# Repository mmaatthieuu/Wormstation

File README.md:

# Wormstation

A fully open-source, all-in-one platform designed for **ease of use** and **accessibility**, yet offering **powerful, highly automated** solutions for laboratory-grade biological research. Wormstation is **ideal for high-throughput workflows** and **streamlined experimental processes**, particularly in _C. elegans_ studies and other small model organisms.

---

## Repositories

- **Wormstation Controller**  
  [GitHub: wormstation_controller](https://github.com/mmaatthieuu/wormstation_controller)  
  A user-friendly GUI that remotely controls the Wormstation Client software. It manages camera and LED settings, schedules recordings, and facilitates error checks or updates—all from a single interface.

- **Wormstation Client**  
  [GitHub: wormstation_client](https://github.com/mmaatthieuu/wormstation_client)  
  The client software running on each Wormstation device (e.g., Raspberry Pi). It handles local camera captures, LED strobing or continuous illumination, data compression, and robust logging routines.

---

## Hardware Overview

Below is an example Wormstation hardware setup, illustrating the 3D-printed housing, integrated cameras, LED arrays, and other key components:

The complete mechanical and electronic designs (including 3D-printable files and KiCad schematics) are maintained in this repository, making the project fully open and reproducible.

---

## Key Features

- **High-Throughput**  
  Record multiple worms in parallel with automated capture schedules and minimal user intervention.
- **Fully Open-Source**  
  All code, hardware designs, and documentation are freely available for community-driven improvements.
- **Modular & Extensible**  
  Easily replace or upgrade components, adapt the software for new experimental protocols, or integrate additional sensors/actuators.
- **Optogenetics & Advanced Illumination**  
  Precisely control IR, blue, and orange LEDs for non-disruptive observation or targeted neural stimulation.
- **Comprehensive Logging**  
  Both the controller and the client track system status, events, and errors, aiding reproducibility and troubleshooting.

---

## Getting Started

1. **Hardware Assembly**  
   - Print the parts (`3D_print/` directory) and assemble according to the provided instructions.
   - Populate the PCB using KiCad files and a bill of materials found in the `electronics/` directory.
   - Mount the cameras, LED rings, or other illumination modules as described in the hardware guides.

2. **Software Installation**  
   - Set up the [Wormstation Client](https://github.com/mmaatthieuu/wormstation_client) on each device (e.g., Raspberry Pi).
   - Use the [Wormstation Controller](https://github.com/mmaatthieuu/wormstation_controller) GUI on your PC for centralized management.

3. **Configuration**  
   - Provide network addresses or hostnames in a `hosts.txt` file so the controller can detect each Wormstation on the LAN or VPN.
   - Customize recording schedules, LED parameters, and log verbosity per your research needs.

4. **Run Experiments**  
   - Start the controller application, select the devices, and define the experimental parameters.
   - Monitor live frames or single-shot previews to check focus/illumination.
   - Retrieve data automatically from each device or store on a NAS for uninterrupted long-term runs.

---

## Contributing

We welcome feedback, bug reports, and pull requests from the community. Please see the individual repositories for guidelines or open a GitHub Issue if you encounter any problems.

---

## License

This project is made available under the [MIT License](LICENSE). We encourage the community to adapt and expand Wormstation for diverse research applications.

---

## Contact

For questions, collaborations, or to share results:

- **Primary Maintainer**: [@mmaatthieuu](https://github.com/mmaatthieuu)  
- **Email**: [\<insert email\>](mailto:someone@example.com)

We look forward to hearing how Wormstation can accelerate your research!

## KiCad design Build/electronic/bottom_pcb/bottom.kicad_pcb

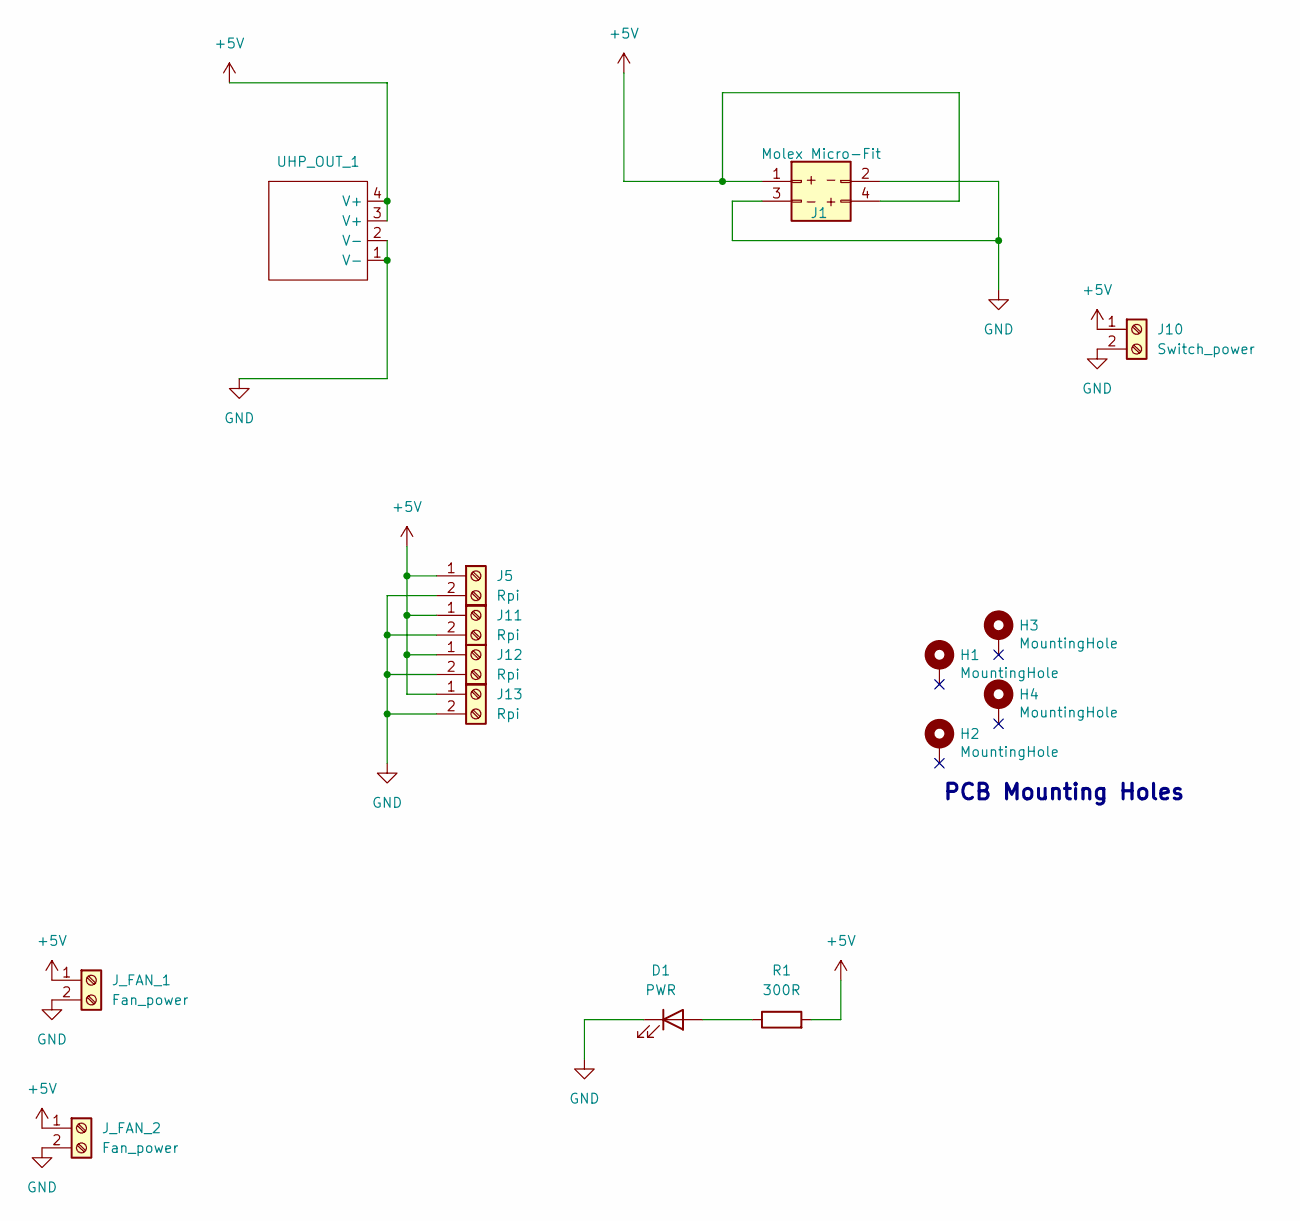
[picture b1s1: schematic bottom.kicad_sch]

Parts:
D1: PWR; LED_D3.0mm
H1, H2, H3, H4: MountingHole; MountingHole_2.2mm_M2_Pad_Via
J1: Molex Micro-Fit; Molex_Micro-Fit_3.0_43045-0400_2x02_P3.00mm_Horizontal; LCSC C122413
J5, J11, J12, J13: Rpi; TerminalBlock_Phoenix_MKDS-1,5-2-5.08_1x02_P5.08mm_Horizont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
J10: Switch_power; TerminalBlock_Phoenix_MKDS-1,5-2-5.08_1x02_P5.08mm_Horizont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
J_FAN_1, J_FAN_2: Fan_power; TerminalBlock_Phoenix_MKDS-1,5-2-5.08_1x02_P5.08mm_Horizont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
R1: 300R; R_Axial_DIN0207_L6.3mm_D2.5mm_P15.24mm_Horizontal
UHP_OUT_1: UHP-200A-5_output

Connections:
+5V: J1.1 (5V), J1.4, J5.1, J10.1, J11.1, J12.1, J13.1, J_FAN_1.1, J_FAN_2.1, R1.2, UHP_OUT_1.3 (V+), UHP_OUT_1.4 (V+)
GND: D1.1 (K), J1.2 (GND), J1.3 (GND), J5.2, J10.2, J11.2, J12.2, J13.2, J_FAN_1.2, J_FAN_2.2, UHP_OUT_1.1 (V-), UHP_OUT_1.2 (V-)
unnamed: D1.2 (A), R1.1

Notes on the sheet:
PCB Mounting Holes

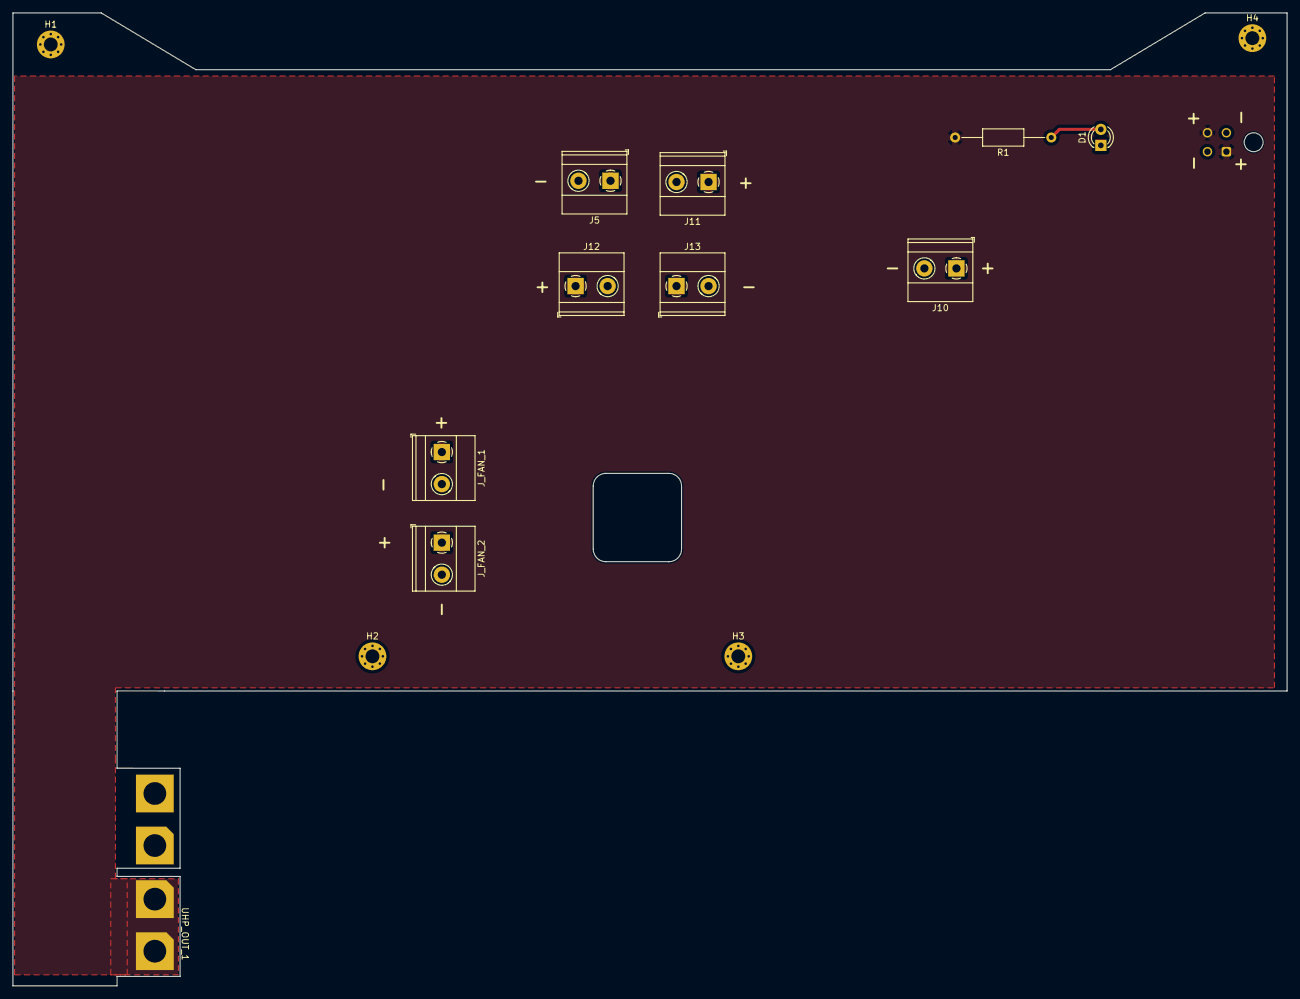
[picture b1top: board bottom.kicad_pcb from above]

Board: 2 copper layers, 202.0 x 154.2 mm, 15 parts (1 on the bottom side), 3 nets.

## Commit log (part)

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2025-02-04 Improve doc and readme
2025-02-06 add kicad and gcode files
